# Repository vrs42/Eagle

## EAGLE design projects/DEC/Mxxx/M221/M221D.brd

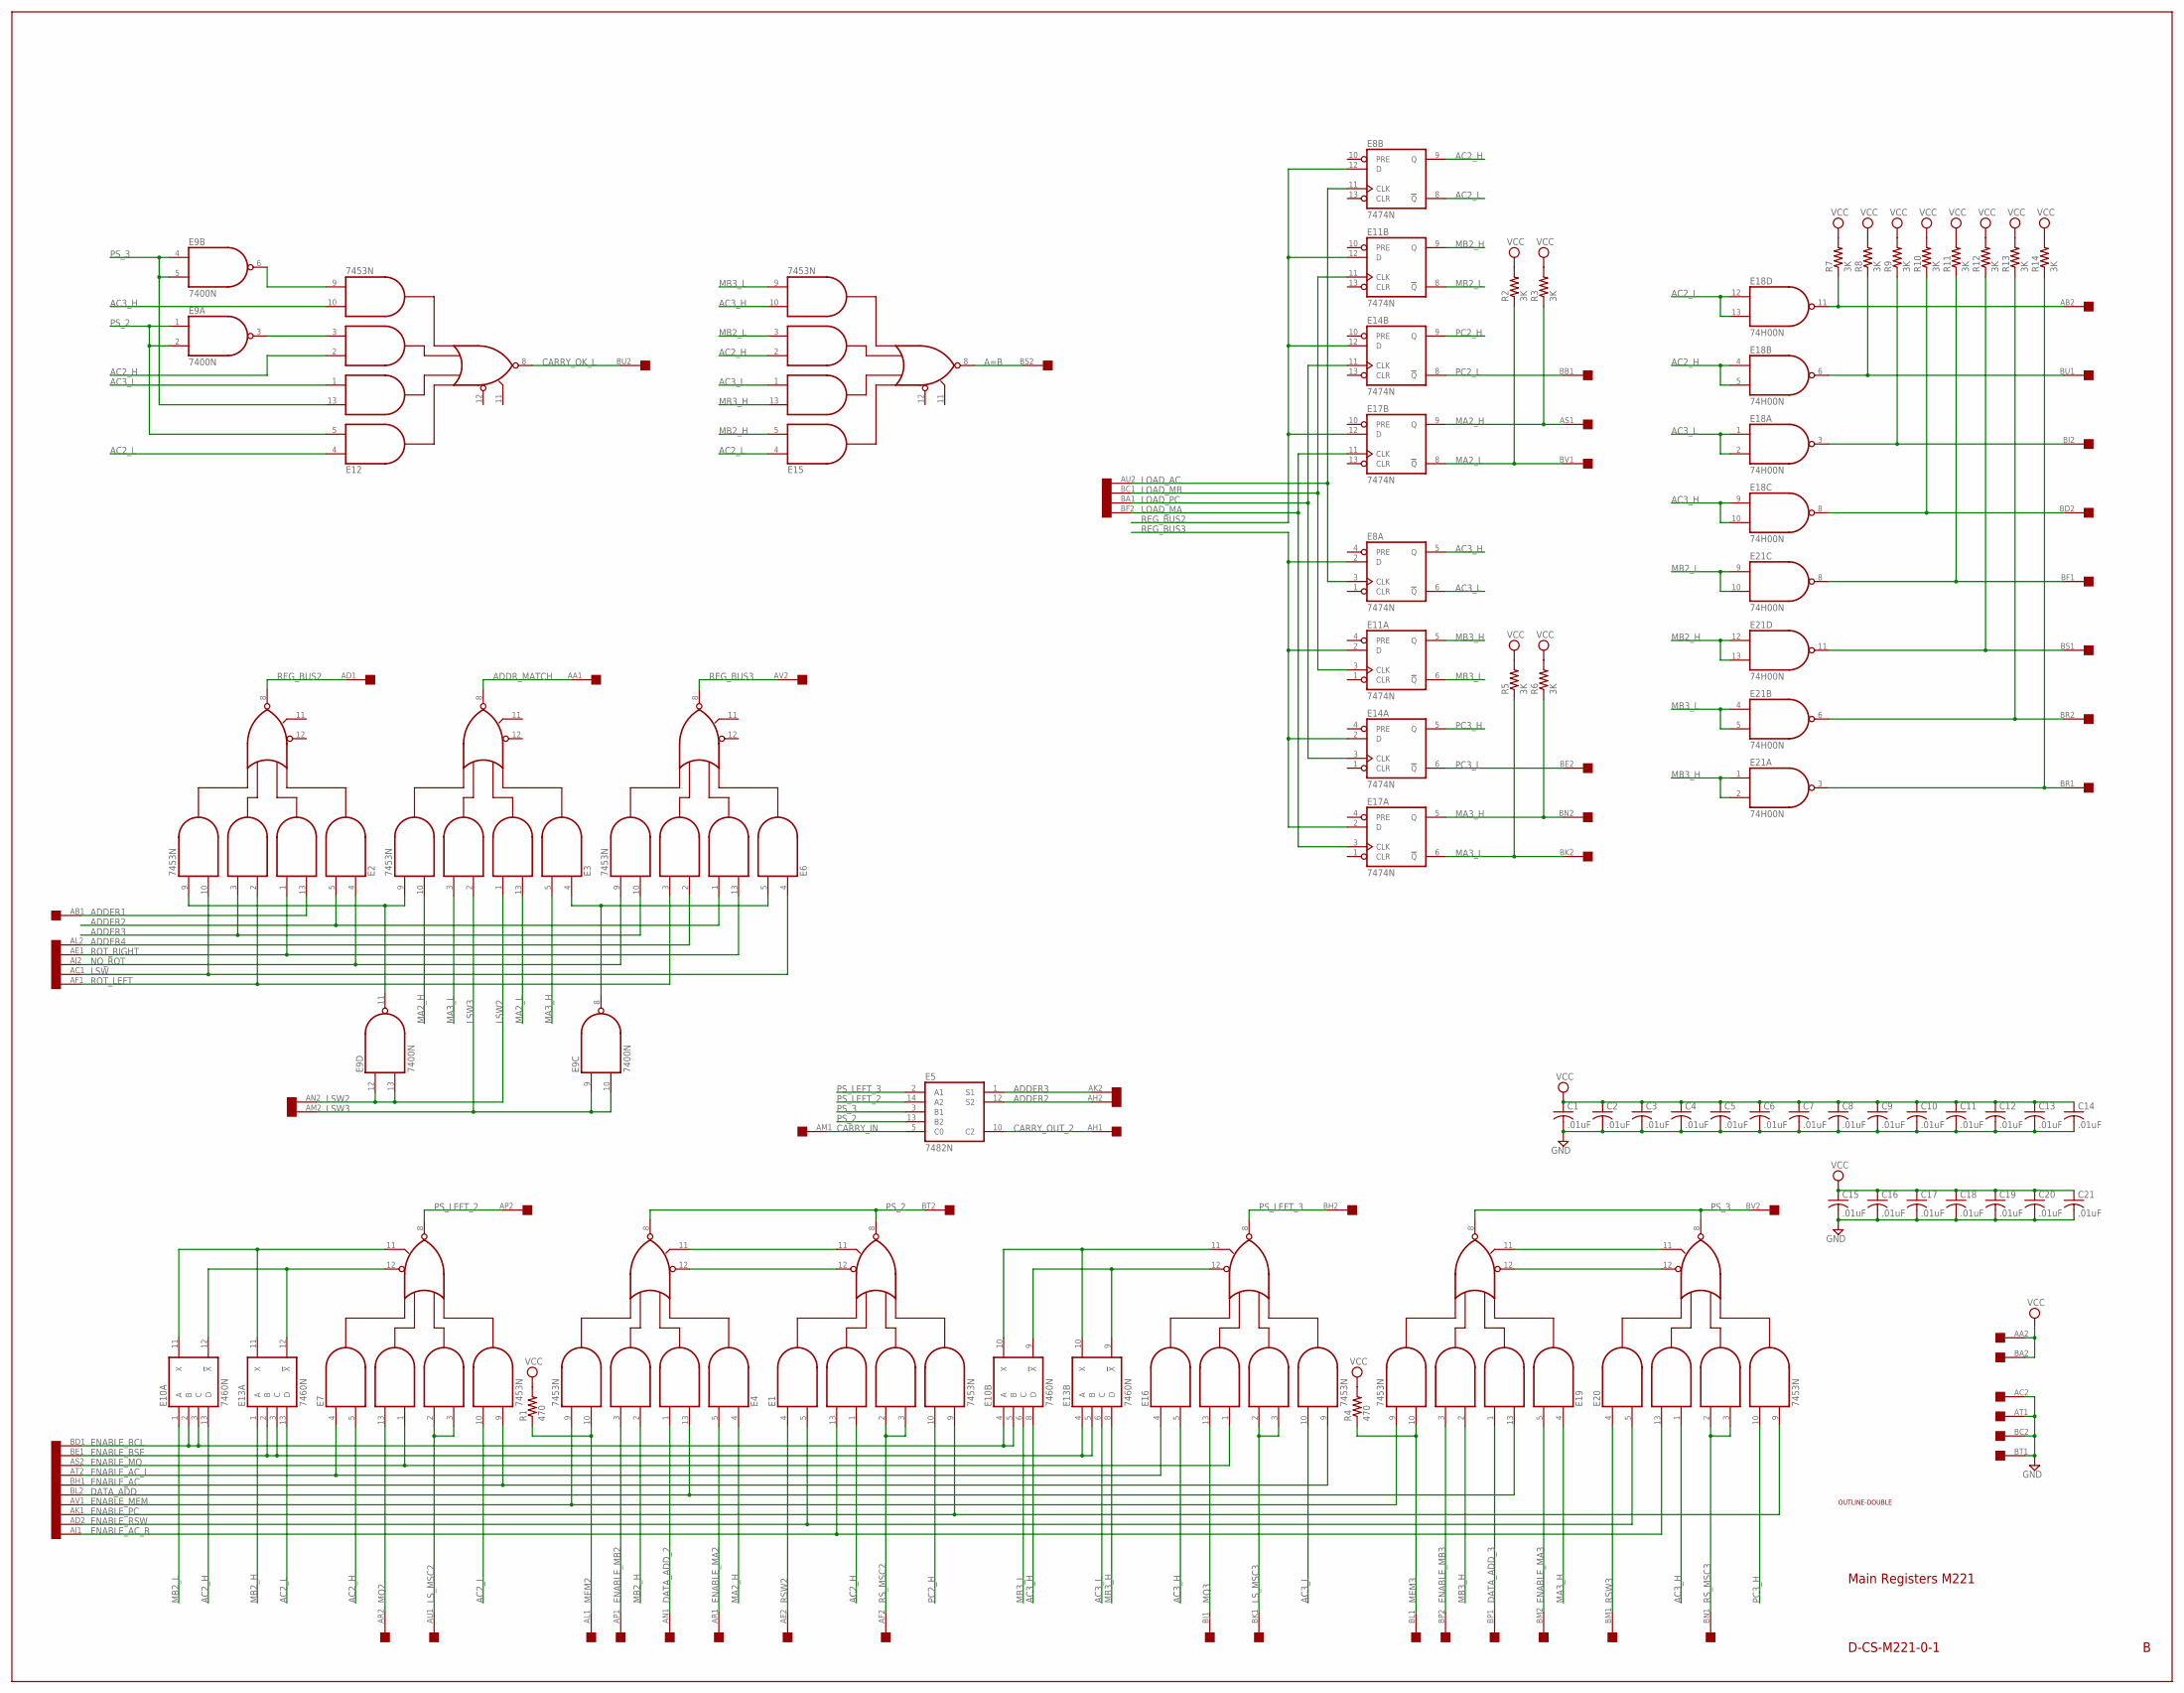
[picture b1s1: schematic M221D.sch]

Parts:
C1, C2, C3, C4, C5, C6, C7, C8, C9, C10, C11, C12, C13, C14, C15, C16, C17, C18, C19, C20, C21: .01uF; C050-025X075
E1, E2, E3, E4, E6, E7, E12, E15, E16, E19, E20: 7453N; DIL14
E5: 7482N; DIL14
E8, E11, E14, E17: 7474N; DIL14
E9: 7400N; DIL14
E10, E13: 7460N; DIL14
E18, E21: 74H00N; DIL14
R1, R4: 470; 0207/10
R2, R3, R5, R6, R7, R8, R9, R10, R11, R12, R13, R14: 3K; 0207/10
U$1: DOUBLE; EDGE-CON4
U$2: OUTLINE-DOUBLE; DOUBLE

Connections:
A=B: E15.8 (O), U$1.BS2
AC2_H: E1.1 (I4), E7.5 (I2), E8.9 (Q), E10.13 (D), E12.2 (I5), E15.2 (I5), E18.4 (I0), E18.5 (I1)
AC2_L: E7.10 (I7), E8.8 (!Q), E12.4 (I1), E13.13 (D), E15.4 (I1), E18.12 (I0), E18.13 (I1)
AC3_H: E8.5 (Q), E10.8 (D), E12.10 (I7), E15.10 (I7), E16.5 (I2), E18.9 (I0), E18.10 (I1), E20.1 (I4)
AC3_L: E8.6 (!Q), E12.1 (I4), E13.6 (C), E15.1 (I4), E16.10 (I7), E18.1 (I0), E18.2 (I1)
ADDER1: E2.13 (I3), U$1.AB1
ADDER2: E2.5 (I2), E5.12 (S2), E6.1 (I4), U$1.AH2
ADDER3: E2.3 (I6), E5.1 (S1), E6.10 (I7), U$1.AK2
ADDER4: E6.2 (I5), U$1.AL2
ADDR_MATCH: E3.8 (O), U$1.AA1
CARRY_IN: E5.5 (C0), U$1.AM1
CARRY_OK_L: E12.8 (O), U$1.BU2
CARRY_OUT_2: E5.10 (C2), U$1.AH1
DATA_ADD: E4.13 (I3), E19.13 (I3), U$1.BL2
DATA_ADD_2: E4.1 (I4), U$1.AN1
DATA_ADD_3: E19.1 (I4), U$1.BP1
ENABLE_AC: E7.9 (I8), E16.9 (I8), U$1.BH1
ENABLE_AC_L: E7.4 (I1), E16.4 (I1), U$1.AT2
ENABLE_AC_R: E1.13 (I3), E20.13 (I3), U$1.AJ1
ENABLE_BCL: E10.2 (B), E10.3 (C), E10.4 (A), E10.5 (B), U$1.BD1
ENABLE_BSE: E13.2 (B), E13.3 (C), E13.4 (A), E13.5 (B), U$1.BE1
ENABLE_MA2: E4.5 (I2), U$1.AR1
ENABLE_MA3: E19.5 (I2), U$1.BM2
ENABLE_MB2: E4.3 (I6), U$1.AP1
ENABLE_MB3: E19.3 (I6), U$1.BP2
ENABLE_MEM: E4.9 (I8), E19.9 (I8), U$1.AV1
ENABLE_MQ: E7.1 (I4), E16.1 (I4), U$1.AS2
ENABLE_PC: E1.9 (I8), E20.9 (I8), U$1.AK1
ENABLE_RSW: E1.5 (I2), E20.5 (I2), U$1.AD2
GND: C1.2, C2.2, C3.2, C4.2, C5.2, C6.2, C7.2, C8.2, C9.2, C10.2, C11.2, C12.2, C13.2, C14.2, C15.2, C16.2, C17.2, C18.2, C19.2, C20.2, C21.2, E1.7 (GND), E2.7 (GND), E3.7 (GND), E4.7 (GND), E5.11 (GND), E6.7 (GND), E7.7 (GND), E8.7 (GND), E9.7 (GND), E10.7 (GND), E11.7 (GND), E12.7 (GND), E13.7 (GND), E14.7 (GND), E15.7 (GND), E16.7 (GND), E17.7 (GND), E18.7 (GND), E19.7 (GND), E20.7 (GND), E21.7 (GND), U$1.AC2, U$1.AT1, U$1.BC2, U$1.BT1
LOAD_AC: E8.3 (CLK), E8.11 (CLK), U$1.AU2
LOAD_MA: E17.3 (CLK), E17.11 (CLK), U$1.BF2
LOAD_MB: E11.3 (CLK), E11.11 (CLK), U$1.BC1
LOAD_PC: E14.3 (CLK), E14.11 (CLK), U$1.BA1
LSW: E2.10 (I7), E6.4 (I1), U$1.AC1
LSW2: E3.1 (I4), E9.12 (I0), E9.13 (I1), U$1.AN2
LSW3: E3.2 (I5), E9.9 (I0), E9.10 (I1), U$1.AM2
LS_MSC2: E7.2 (I5), E7.3 (I6), U$1.AU1
LS_MSC3: E16.2 (I5), E16.3 (I6), U$1.BK1
MA2_H: E3.10 (I7), E4.4 (I1), E17.9 (Q), R3.1, U$1.AS1
MA2_L: E3.13 (I3), E17.8 (!Q), R2.1, U$1.BV1
MA3_H: E3.5 (I2), E17.5 (Q), E19.4 (I1), R6.1, U$1.BN2
MA3_L: E3.3 (I6), E17.6 (!Q), R5.1, U$1.BK2
MB2_H: E4.2 (I5), E11.9 (Q), E13.1 (A), E15.5 (I2), E21.12 (I0), E21.13 (I1)
MB2_L: E10.1 (A), E11.8 (!Q), E15.3 (I6), E21.9 (I0), E21.10 (I1)
MB3_H: E11.5 (Q), E13.8 (D), E15.13 (I3), E19.2 (I5), E21.1 (I0), E21.2 (I1)
MB3_L: E10.6 (C), E11.6 (!Q), E15.9 (I8), E21.4 (I0), E21.5 (I1)
MEM2: E4.10 (I7), R1.1, U$1.AL1
MEM3: E19.10 (I7), R4.1, U$1.BL1
MQ2: E7.13 (I3), U$1.AR2
MQ3: E16.13 (I3), U$1.BJ1
unnamed: E10.10 (X), E13.10 (X), E16.11 (I10)
unnamed: E10.9 (!X), E13.9 (!X), E16.12 (I9)
unnamed: E1.11 (I10), E4.11 (I10)
unnamed: E1.12 (I9), E4.12 (I9)
unnamed: E7.12 (I9), E10.12 (!X), E13.12 (!X)
unnamed: E7.11 (I10), E10.11 (X), E13.11 (X)
unnamed: E19.12 (I9), E20.12 (I9)
unnamed: E19.11 (I10), E20.11 (I10)
unnamed: E2.9 (I8), E3.9 (I8), E9.11 (O)
unnamed: E3.4 (I1), E6.5 (I2), E9.8 (O)
unnamed: E18.11 (O), R7.1, U$1.AB2
unnamed: E18.6 (O), R8.1, U$1.BU1
unnamed: E18.3 (O), R9.1, U$1.BJ2
unnamed: E18.8 (O), R10.1, U$1.BD2
unnamed: E21.8 (O), R11.1, U$1.BF1
unnamed: E21.11 (O), R12.1, U$1.BS1
unnamed: E21.6 (O), R13.1, U$1.BR2
unnamed: E21.3 (O), R14.1, U$1.BR1
unnamed: E9.3 (O), E12.3 (I6)
unnamed: E9.6 (O), E12.9 (I8)
NO_ROT: E2.4 (I1), E6.9 (I8), U$1.AJ2
PC2_H: E1.10 (I7), E14.9 (Q)
PC2_L: E14.8 (!Q), U$1.BB1
PC3_H: E14.5 (Q), E20.10 (I7)
PC3_L: E14.6 (!Q), U$1.BE2
PS_2: E1.8 (O), E4.8 (O), E5.13 (B2), E9.1 (I0), E9.2 (I1), E12.5 (I2), U$1.BT2
PS_3: E5.3 (B1), E9.4 (I0), E9.5 (I1), E12.13 (I3), E19.8 (O), E20.8 (O), U$1.BV2
PS_LEFT_2: E5.14 (A2), E7.8 (O), U$1.AP2
PS_LEFT_3: E5.2 (A1), E16.8 (O), U$1.BH2
REG_BUS2: E2.8 (O), E8.12 (D), E11.12 (D), E14.12 (D), E17.12 (D), U$1.AD1
REG_BUS3: E6.8 (O), E8.2 (D), E11.2 (D), E14.2 (D), E17.2 (D), U$1.AV2
ROT_LEFT: E2.2 (I5), E6.3 (I6), U$1.AF1
ROT_RIGHT: E2.1 (I4), E6.13 (I3), U$1.AE1
RSW2: E1.4 (I1), U$1.AE2
RSW3: E20.4 (I1), U$1.BM1
RS_MSC2: E1.2 (I5), E1.3 (I6), U$1.AF2
RS_MSC3: E20.2 (I5), E20.3 (I6), U$1.BN1
VCC: C1.1, C2.1, C3.1, C4.1, C5.1, C6.1, C7.1, C8.1, C9.1, C10.1, C11.1, C12.1, C13.1, C14.1, C15.1, C16.1, C17.1, C18.1, C19.1, C20.1, C21.1, E1.14 (VCC), E2.14 (VCC), E3.14 (VCC), E4.14 (VCC), E5.4 (VCC), E6.14 (VCC), E7.14 (VCC), E8.14 (VCC), E9.14 (VCC), E10.14 (VCC), E11.14 (VCC), E12.14 (VCC), E13.14 (VCC), E14.14 (VCC), E15.14 (VCC), E16.14 (VCC), E17.14 (VCC), E18.14 (VCC), E19.14 (VCC), E20.14 (VCC), E21.14 (VCC), R1.2, R2.2, R3.2, R4.2, R5.2, R6.2, R7.2, R8.2, R9.2, R10.2, R11.2, R12.2, R13.2, R14.2, U$1.AA2, U$1.BA2

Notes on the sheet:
Main Registers M221
D-CS-M221-0-1

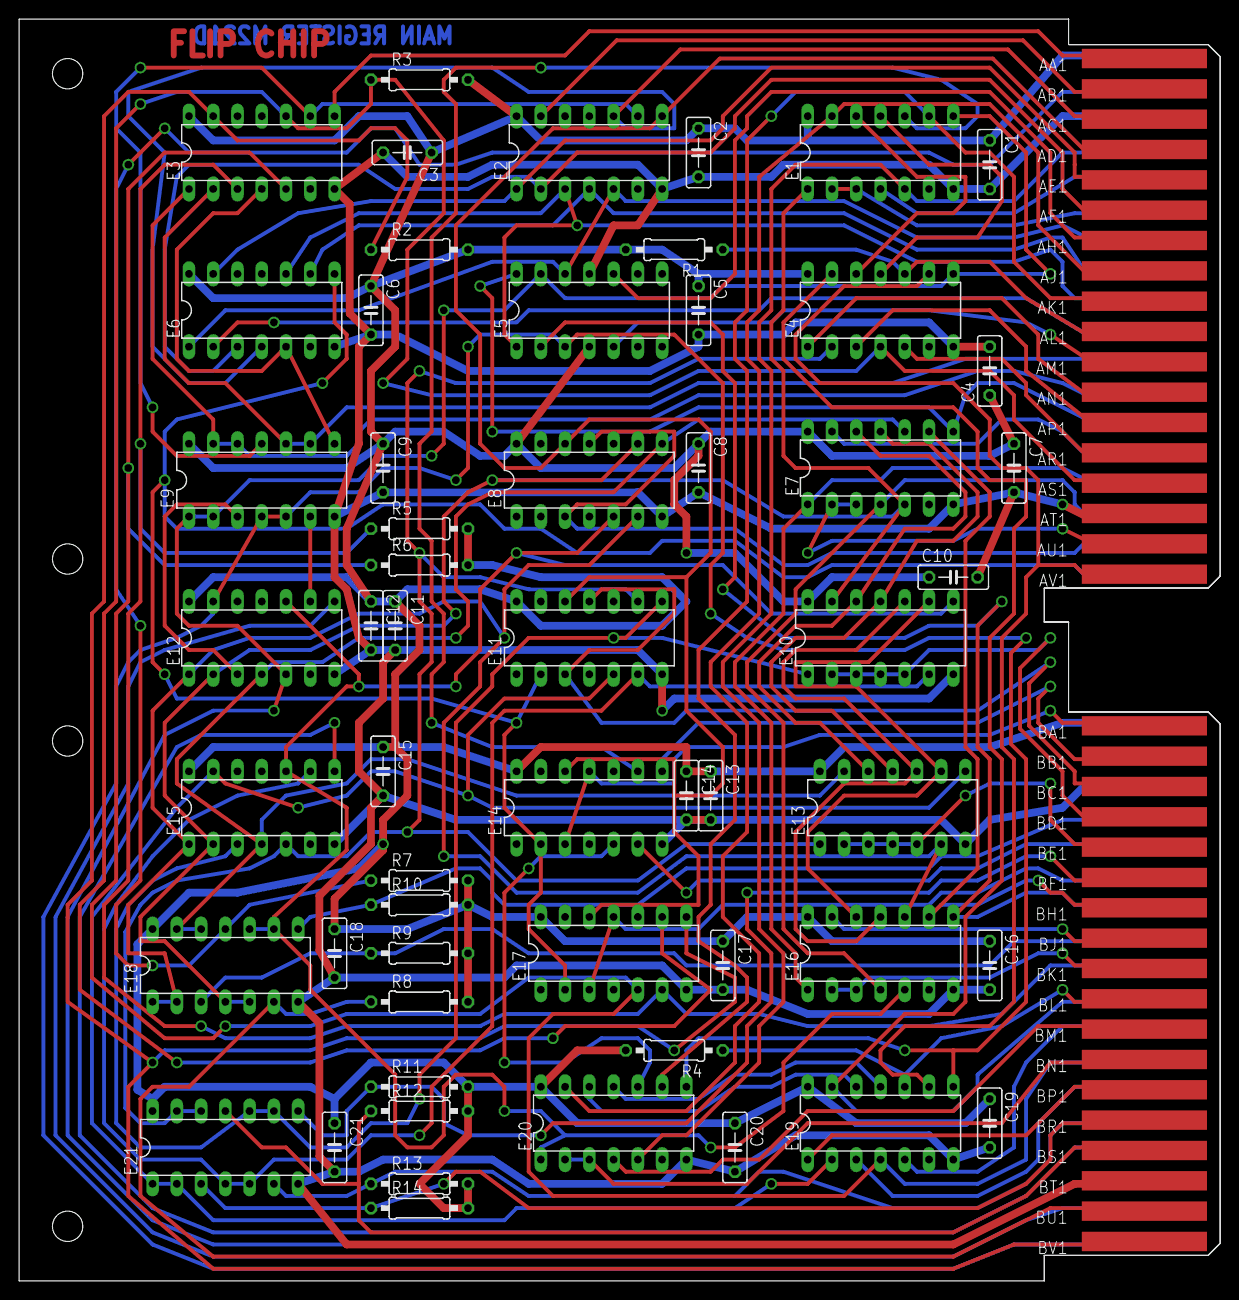
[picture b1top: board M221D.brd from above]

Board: 2 copper layers, 125.7 x 132.1 mm, 58 parts (0 on the bottom side), 89 nets.

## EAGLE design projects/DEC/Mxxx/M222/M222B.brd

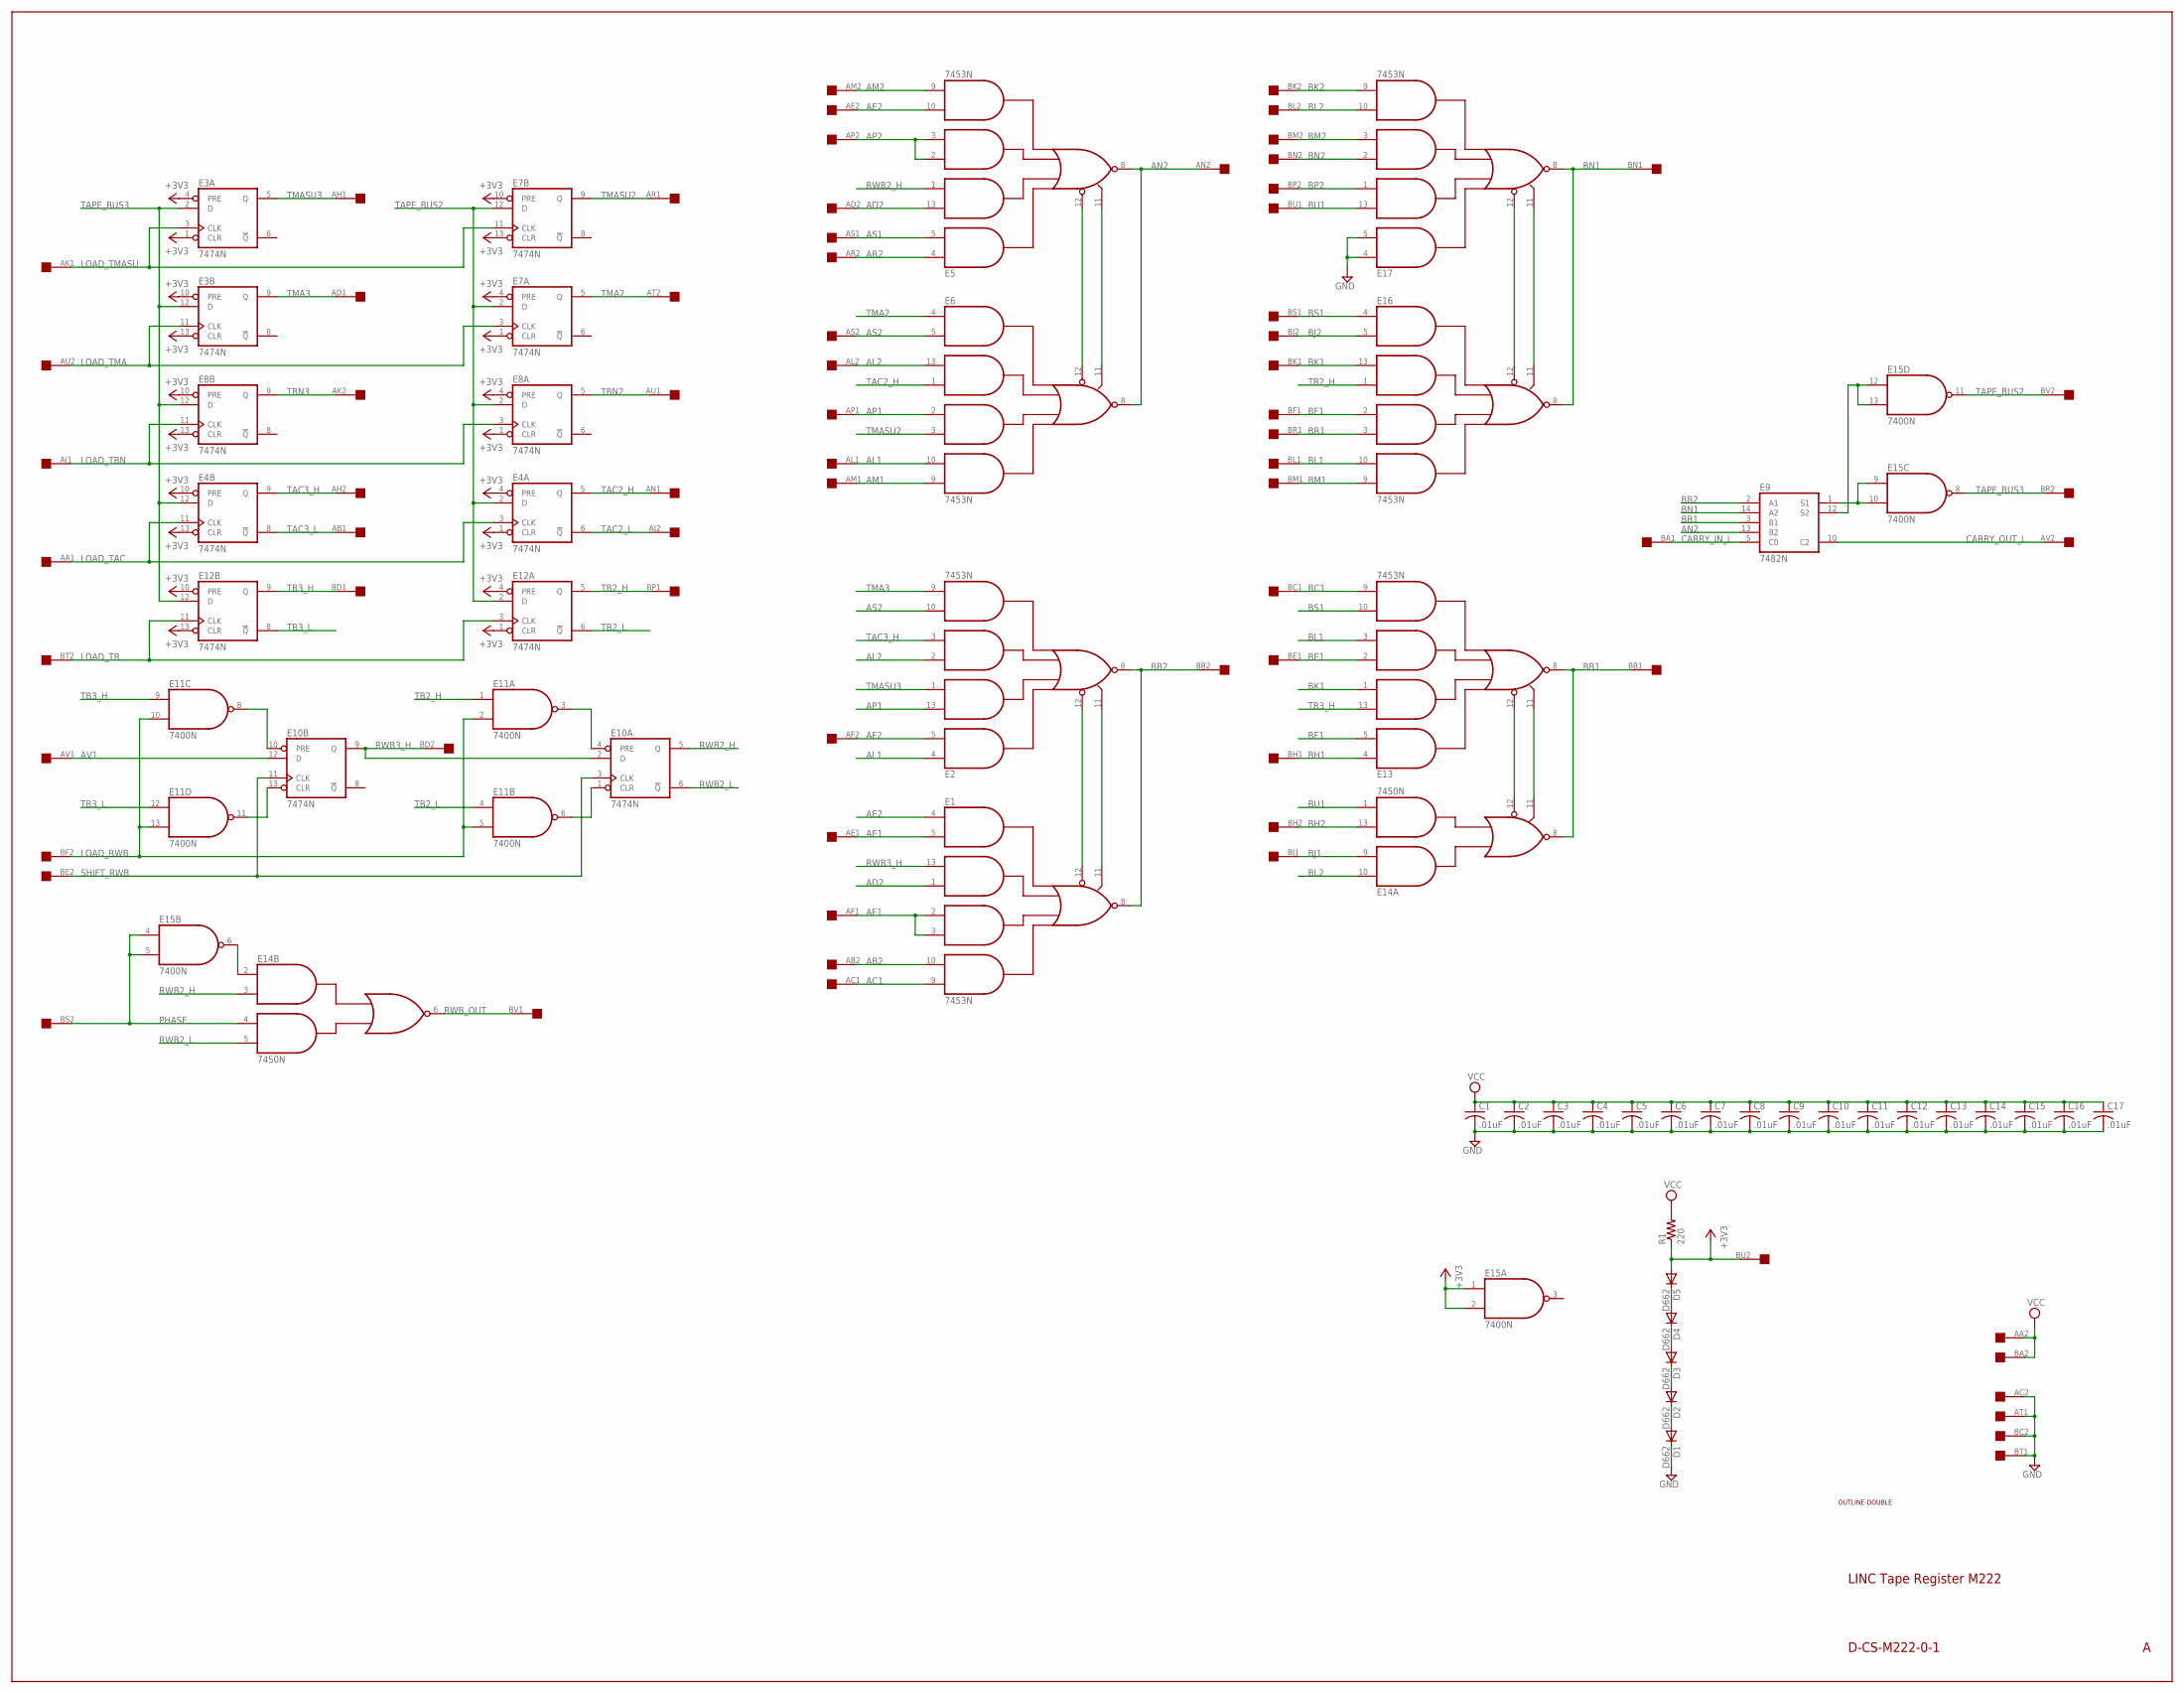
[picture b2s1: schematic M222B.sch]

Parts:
C1, C2, C3, C4, C5, C6, C7, C8, C9, C10, C11, C12, C13, C14, C15, C16, C17: .01uF; C050-025X075
D1, D2, D3, D4, D5: D662; DO35-10
E1, E2, E5, E6, E13, E16, E17: 7453N; DIL14
E3, E4, E7, E8, E10, E12: 7474N; DIL14
E9: 7482N; DIL14
E11, E15: 7400N; DIL14
E14: 7450N; DIL14
R1: 220; 0207/10
U$1: DOUBLE; EDGE-CON4
U$2: OUTLINE-DOUBLE; DOUBLE

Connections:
+3V3: D5.A, E3.1 (CLR), E3.4 (PRE), E3.10 (PRE), E3.13 (CLR), E4.1 (CLR), E4.4 (PRE), E4.10 (PRE), E4.13 (CLR), E7.1 (CLR), E7.4 (PRE), E7.10 (PRE), E7.13 (CLR), E8.1 (CLR), E8.4 (PRE), E8.10 (PRE), E8.13 (CLR), E12.1 (CLR), E12.4 (PRE), E12.10 (PRE), E12.13 (CLR), E15.1 (I0), E15.2 (I1), R1.1, U$1.BU2
AB2: E1.10 (I7), U$1.AB2
AC1: E1.9 (I8), U$1.AC1
AD2: E1.1 (I4), E5.13 (I3), U$1.AD2
AE1: E1.5 (I2), U$1.AE1
AE2: E1.4 (I1), E5.10 (I7), U$1.AE2
AF1: E1.2 (I5), E1.3 (I6), U$1.AF1
AF2: E2.5 (I2), U$1.AF2
AL1: E2.4 (I1), E6.10 (I7), U$1.AL1
AL2: E2.2 (I5), E6.13 (I3), U$1.AL2
AM1: E6.9 (I8), U$1.AM1
AM2: E5.9 (I8), U$1.AM2
AN2: E5.8 (O), E6.8 (O), E9.13 (B2), U$1.AN2
AP1: E2.13 (I3), E6.2 (I5), U$1.AP1
AP2: E5.2 (I5), E5.3 (I6), U$1.AP2
AR2: E5.4 (I1), U$1.AR2
AS1: E5.5 (I2), U$1.AS1
AS2: E2.10 (I7), E6.5 (I2), U$1.AS2
AV1: E10.12 (D), U$1.AV1
BB1: E9.3 (B1), E13.8 (O), E14.8 (O), U$1.BB1
BB2: E1.8 (O), E2.8 (O), E9.2 (A1), U$1.BB2
BC1: E13.9 (I8), U$1.BC1
BE1: E13.2 (I5), U$1.BE1
BF1: E13.5 (I2), E16.2 (I5), U$1.BF1
BH1: E13.4 (I1), U$1.BH1
BH2: E14.13 (I3), U$1.BH2
BJ1: E14.9 (I2), U$1.BJ1
BJ2: E16.5 (I2), U$1.BJ2
BK1: E13.1 (I4), E16.13 (I3), U$1.BK1
BK2: E17.9 (I8), U$1.BK2
BL1: E13.3 (I6), E16.10 (I7), U$1.BL1
BL2: E14.10 (I1), E17.10 (I7), U$1.BL2
BM1: E16.9 (I8), U$1.BM1
BM2: E17.3 (I6), U$1.BM2
BN1: E9.14 (A2), E16.8 (O), E17.8 (O), U$1.BN1
BN2: E17.2 (I5), U$1.BN2
BP2: E17.1 (I4), U$1.BP2
BR1: E16.3 (I6), U$1.BR1
BS1: E13.10 (I7), E16.4 (I1), U$1.BS1
BU1: E14.1 (I4), E17.13 (I3), U$1.BU1
CARRY_IN_L: E9.5 (C0), U$1.BA1
CARRY_OUT_L: E9.10 (C2), U$1.AV2
GND: C1.2, C2.2, C3.2, C4.2, C5.2, C6.2, C7.2, C8.2, C9.2, C10.2, C11.2, C12.2, C13.2, C14.2, C15.2, C16.2, C17.2, D1.C, E1.7 (GND), E2.7 (GND), E3.7 (GND), E4.7 (GND), E5.7 (GND), E6.7 (GND), E7.7 (GND), E8.7 (GND), E9.11 (GND), E10.7 (GND), E11.7 (GND), E12.7 (GND), E13.7 (GND), E14.7 (GND), E15.7 (GND), E16.7 (GND), E17.4 (I1), E17.5 (I2), E17.7 (GND), U$1.AC2, U$1.AT1, U$1.BC2, U$1.BT1
LOAD_RWB: E11.2 (I1), E11.5 (I1), E11.10 (I1), E11.13 (I1), U$1.BF2
LOAD_TAC: E4.3 (CLK), E4.11 (CLK), U$1.AA1
LOAD_TB: E12.3 (CLK), E12.11 (CLK), U$1.BT2
LOAD_TBN: E8.3 (CLK), E8.11 (CLK), U$1.AJ1
LOAD_TMA: E3.11 (CLK), E7.3 (CLK), U$1.AU2
LOAD_TMASU: E3.3 (CLK), E7.11 (CLK), U$1.AK1
unnamed: E9.1 (S1), E15.9 (I0), E15.10 (I1)
unnamed: E9.12 (S2), E15.12 (I0), E15.13 (I1)
unnamed: E1.12 (I9), E2.12 (I9)
unnamed: E1.11 (I10), E2.11 (I10)
unnamed: E5.11 (I10), E6.11 (I10)
unnamed: E5.12 (I9), E6.12 (I9)
unnamed: E10.13 (CLR), E11.11 (O)
unnamed: E10.10 (PRE), E11.8 (O)
unnamed: E16.12 (I9), E17.12 (I9)
unnamed: E16.11 (I10), E17.11 (I10)
unnamed: D4.A, D5.C
unnamed: E13.12 (I9), E14.12 (I5)
unnamed: E13.11 (I10), E14.11 (I6)
unnamed: D1.A, D2.C
unnamed: E14.2 (I1), E15.6 (O)
unnamed: E10.4 (PRE), E11.3 (O)
unnamed: E10.1 (CLR), E11.6 (O)
unnamed: D2.A, D3.C
unnamed: D3.A, D4.C
PHASE: E14.4 (I3), E15.4 (I0), E15.5 (I1), U$1.BS2
RWB2_H: E5.1 (I4), E10.5 (Q), E14.3 (I2)
RWB2_L: E10.6 (!Q), E14.5 (I4)
RWB3_H: E1.13 (I3), E10.2 (D), E10.9 (Q), U$1.BD2
RWB_OUT: E14.6 (O), U$1.BV1
SHIFT_RWB: E10.3 (CLK), E10.11 (CLK), U$1.BE2
TAC2_H: E4.5 (Q), E6.1 (I4), U$1.AN1
TAC2_L: E4.6 (!Q), U$1.AJ2
TAC3_H: E2.3 (I6), E4.9 (Q), U$1.AH2
TAC3_L: E4.8 (!Q), U$1.AB1
TAPE_BUS2: E4.2 (D), E7.2 (D), E7.12 (D), E8.2 (D), E12.2 (D), E15.11 (O), U$1.BV2
TAPE_BUS3: E3.2 (D), E3.12 (D), E4.12 (D), E8.12 (D), E12.12 (D), E15.8 (O), U$1.BR2
TB2_H: E11.1 (I0), E12.5 (Q), E16.1 (I4), U$1.BP1
TB2_L: E11.4 (I0), E12.6 (!Q)
TB3_H: E11.9 (I0), E12.9 (Q), E13.13 (I3), U$1.BD1
TB3_L: E11.12 (I0), E12.8 (!Q)
TBN2: E8.5 (Q), U$1.AU1
TBN3: E8.9 (Q), U$1.AK2
TMA2: E6.4 (I1), E7.5 (Q), U$1.AT2
TMA3: E2.9 (I8), E3.9 (Q), U$1.AD1
TMASU2: E6.3 (I6), E7.9 (Q), U$1.AR1
TMASU3: E2.1 (I4), E3.5 (Q), U$1.AH1
VCC: C1.1, C2.1, C3.1, C4.1, C5.1, C6.1, C7.1, C8.1, C9.1, C10.1, C11.1, C12.1, C13.1, C14.1, C15.1, C16.1, C17.1, E1.14 (VCC), E2.14 (VCC), E3.14 (VCC), E4.14 (VCC), E5.14 (VCC), E6.14 (VCC), E7.14 (VCC), E8.14 (VCC), E9.4 (VCC), E10.14 (VCC), E11.14 (VCC), E12.14 (VCC), E13.14 (VCC), E14.14 (VCC), E15.14 (VCC), E16.14 (VCC), E17.14 (VCC), R1.2, U$1.AA2, U$1.BA2

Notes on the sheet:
LINC Tape Register M222
D-CS-M222-0-1

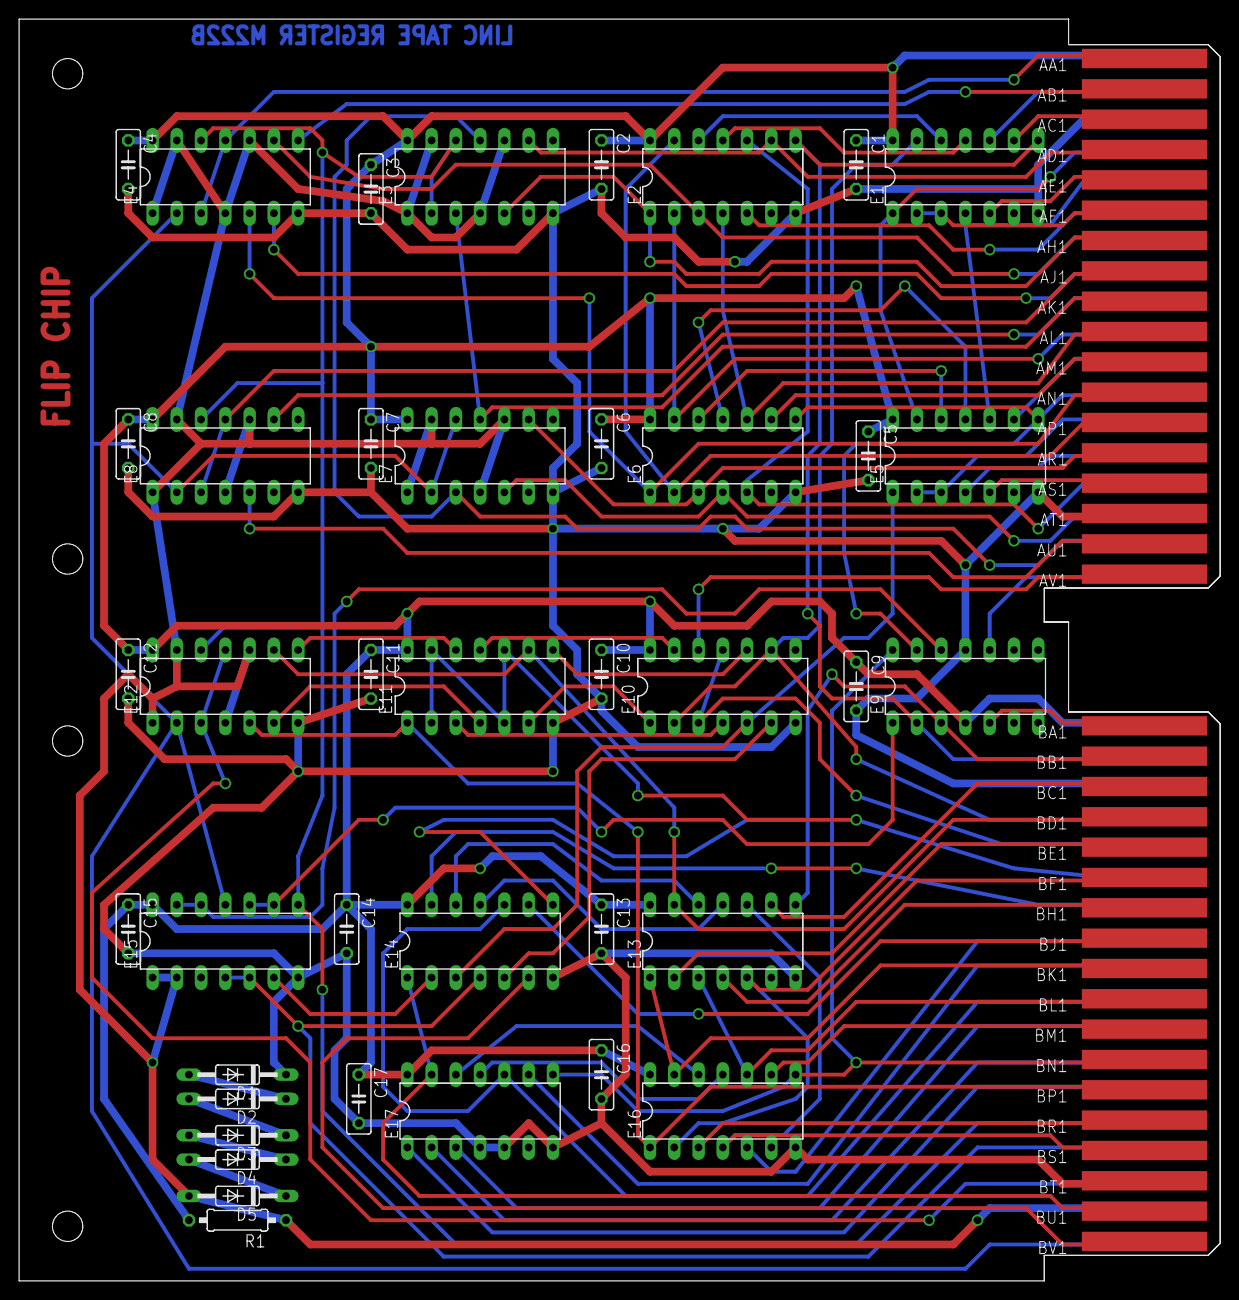
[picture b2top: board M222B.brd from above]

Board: 2 copper layers, 125.7 x 132.1 mm, 43 parts (0 on the bottom side), 91 nets.

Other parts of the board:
U$4: FLIPCHIP

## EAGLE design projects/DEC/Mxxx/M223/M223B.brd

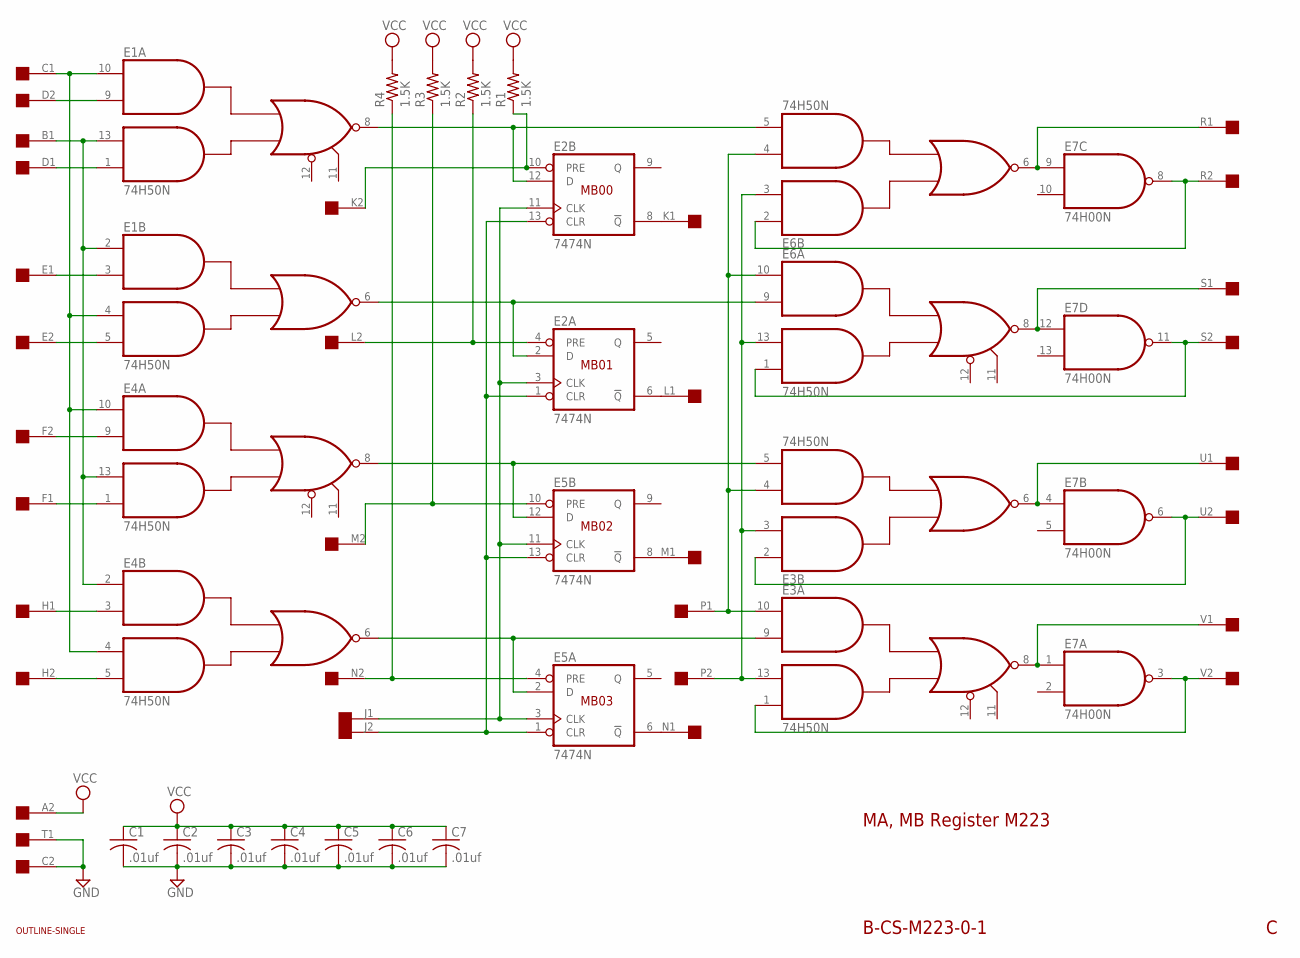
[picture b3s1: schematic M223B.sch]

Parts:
C1, C2, C3, C4, C5, C6, C7: .01uf; C050-025X075
E1, E3, E4, E6: 74H50N; DIL14
E2, E5: 7474N; DIL14
E7: 74H00N; DIL14
R1, R2, R3, R4: 1.5K; 0207/10
U$1: OUTLINE-SINGLE; SINGLE
U$4: SINGLE; EDGE-CON2

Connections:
GND: C1.2, C2.2, C3.2, C4.2, C5.2, C6.2, C7.2, E1.7 (GND), E2.7 (GND), E3.7 (GND), E4.7 (GND), E5.7 (GND), E6.7 (GND), E7.7 (GND), U$4.C2, U$4.T1
unnamed: E1.6 (O), E2.2 (D), E6.9 (I2)
unnamed: E1.8 (O), E2.12 (D), E6.5 (I4)
unnamed: E3.8 (O), E7.1 (I0), U$4.V1
unnamed: E1.1 (I4), U$4.D1
unnamed: E1.9 (I2), U$4.D2
unnamed: E1.2 (I1), E1.13 (I3), E4.2 (I1), E4.13 (I3), U$4.B1
unnamed: E1.4 (I3), E1.10 (I1), E4.4 (I3), E4.10 (I1), U$4.C1
unnamed: E1.3 (I2), U$4.E1
unnamed: E1.5 (I4), U$4.E2
unnamed: E4.1 (I4), U$4.F1
unnamed: E4.3 (I2), U$4.H1
unnamed: E4.9 (I2), U$4.F2
unnamed: E4.5 (I4), U$4.H2
unnamed: E3.5 (I4), E4.8 (O), E5.12 (D)
unnamed: E3.9 (I2), E4.6 (O), E5.2 (D)
unnamed: E3.6 (O), E7.4 (I0), U$4.U1
unnamed: E6.8 (O), E7.12 (I0), U$4.S1
unnamed: E6.6 (O), E7.9 (I0), U$4.R1
unnamed: E2.8 (!Q), U$4.K1
unnamed: E2.6 (!Q), U$4.L1
unnamed: E5.8 (!Q), U$4.M1
unnamed: E5.6 (!Q), U$4.N1
unnamed: E2.3 (CLK), E2.11 (CLK), E5.3 (CLK), E5.11 (CLK), U$4.J1
unnamed: E2.1 (CLR), E2.13 (CLR), E5.1 (CLR), E5.13 (CLR), U$4.J2
unnamed: E2.10 (PRE), R1.1, U$4.K2
unnamed: E5.4 (PRE), R4.1, U$4.N2
unnamed: E5.10 (PRE), R3.1, U$4.M2
unnamed: E2.4 (PRE), R2.1, U$4.L2
unnamed: E3.3 (I2), E3.13 (I3), E6.3 (I2), E6.13 (I3), U$4.P2
unnamed: E3.4 (I3), E3.10 (I1), E6.4 (I3), E6.10 (I1), U$4.P1
unnamed: E3.1 (I4), E7.3 (O), U$4.V2
unnamed: E3.2 (I1), E7.6 (O), U$4.U2
unnamed: E6.1 (I4), E7.11 (O), U$4.S2
unnamed: E6.2 (I1), E7.8 (O), U$4.R2
VCC: C1.1, C2.1, C3.1, C4.1, C5.1, C6.1, C7.1, E1.14 (VCC), E2.14 (VCC), E3.14 (VCC), E4.14 (VCC), E5.14 (VCC), E6.14 (VCC), E7.14 (VCC), R1.2, R2.2, R3.2, R4.2, U$4.A2

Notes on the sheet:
B-CS-M223-0-1
MA, MB Register M223
MB00
MB01
MB02
MB03

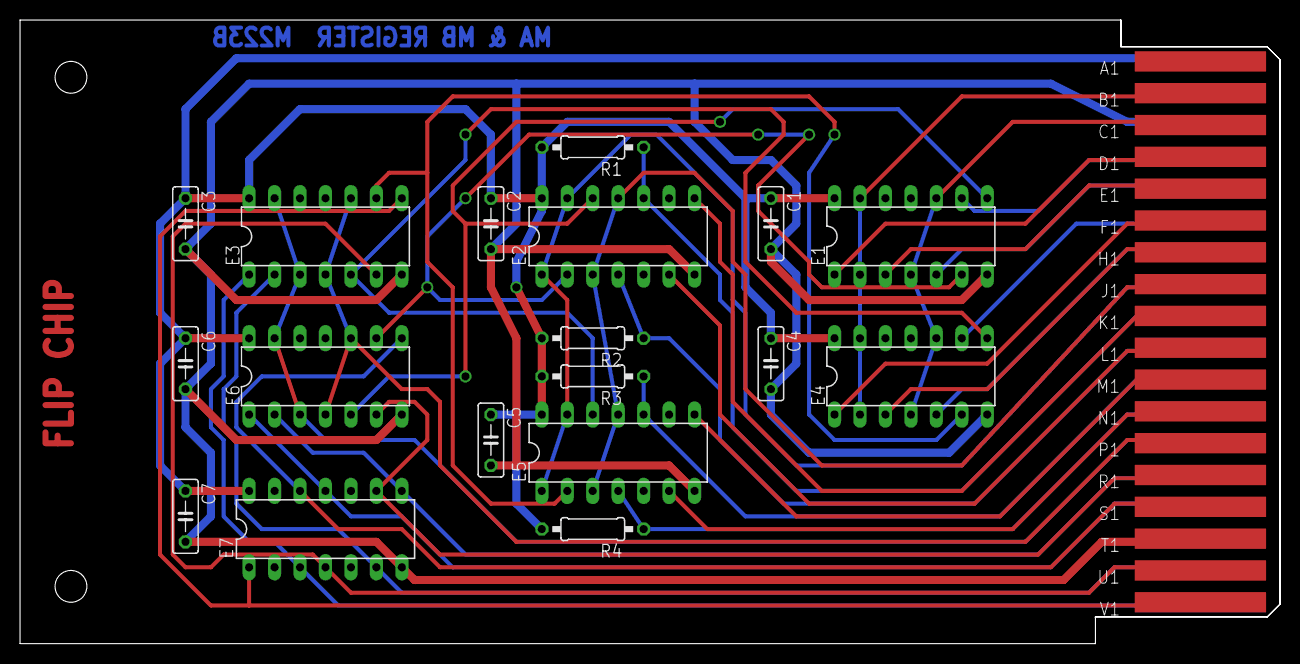
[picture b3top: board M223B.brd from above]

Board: 2 copper layers, 125.7 x 62.2 mm, 21 parts (0 on the bottom side), 36 nets.

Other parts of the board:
U$5: FLIPCHIP
